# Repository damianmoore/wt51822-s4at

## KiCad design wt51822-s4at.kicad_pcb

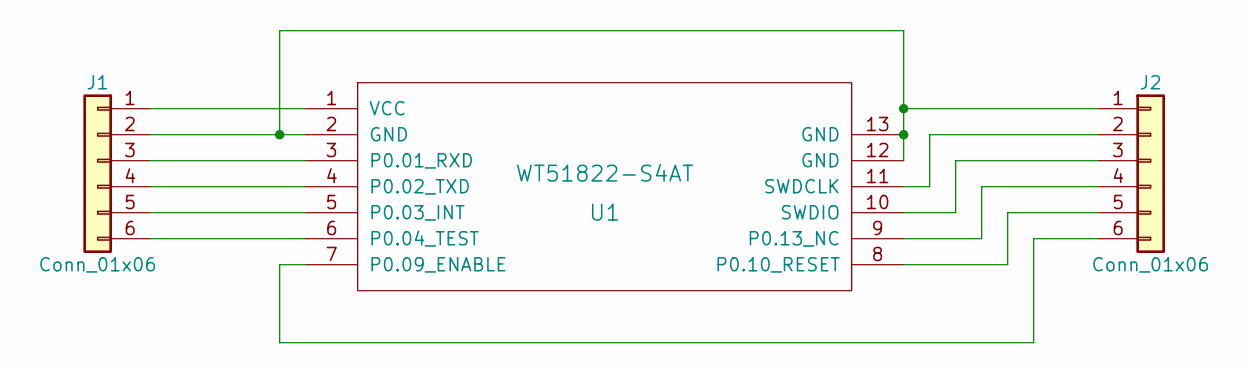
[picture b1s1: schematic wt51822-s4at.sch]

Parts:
J1, J2: Conn_01x06; Pin_Header_Straight_Simplified_1x06_Pitch2.54mm
U1: WT51822-S4AT

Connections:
unnamed: J1.1, U1.1 (VCC)
unnamed: J1.2, J2.1, U1.2 (GND), U1.12 (GND), U1.13 (GND)
unnamed: J1.3, U1.3 (P0.01_RXD)
unnamed: J1.4, U1.4 (P0.02_TXD)
unnamed: J1.5, U1.5 (P0.03_INT)
unnamed: J1.6, U1.6 (P0.04_TEST)
unnamed: J2.2, U1.11 (SWDCLK)
unnamed: J2.3, U1.10 (SWDIO)
unnamed: J2.4, U1.9 (P0.13_NC)
unnamed: J2.5, U1.8 (P0.10_RESET)
unnamed: J2.6, U1.7 (P0.09_ENABLE)

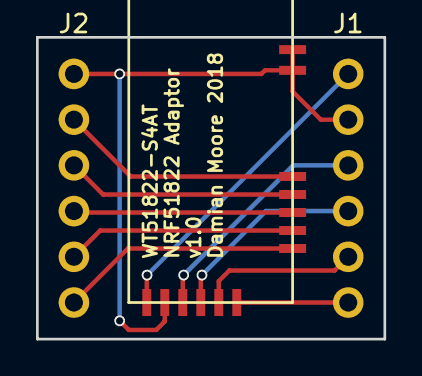
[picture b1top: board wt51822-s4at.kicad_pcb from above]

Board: 2 copper layers, 19.3 x 16.8 mm, 3 parts (0 on the bottom side), 11 nets.

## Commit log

2018-06-01 Adaptor to allow use of the WT51822-S4AT NRF51822 Bluetooth module
